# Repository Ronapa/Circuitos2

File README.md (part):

# Trabajo Práctico de Diseño
## Diseño de Circuitos Electronicos (86.10) - Primer cuatrimestre 2019
## Diseño de un Circuito amplificador clase G paralelo.
#### Integrantes: 
#####  Rodrigo Nahuel Parra - Padrón: 98785 - email: [ro.nahuel95@gmail.com](mailto:ro.nahuel95@gmail.com)
#####  Gonzalo Gilces Duran - Padrón: 99074 - email: [gonzalo.gilces@hotmail.com](mailto:gonzalo.gilces@hotmail.com)
#####  Segundo Molina Abeniacar - Padrón: 99306 - email: [segun_m@hotmail.com](mailto:segun_m@hotmail.com)
#### Tutor:
##### Edgardo Marchi - email: [edgardo.marchi@gmail.com](mailto:edgardo.marchi@gmail.com)

#### Índice
* [Resumen](https://github.com/Ronapa/Circuitos2/#resumen)  
* [Diseño](https://github.com/Ronapa/Circuitos2/#diseño)  
  * [Polarización y funcionamiento del circuito](https://github.com/Ronapa/Circuitos2/#polarización-y-funcionamiento-del-circuito)  
    * [Etapa de entrada](https://github.com/Ronapa/Circuitos2/#etapa-de-entrada)  
    * [Etapa VAS y multiplicador de Vbe](https://github.com/Ronapa/Circuitos2/#etapa-vas-y-multiplicador-de-vbe)
    * [Etapa de salida](https://github.com/Ronapa/Circuitos2/#etapa-de-salida)
    * [Switches y conmutación](https://github.com/Ronapa/Circuitos2/#switches-y-conmutación)
    * [Fuentes switching](https://github.com/Ronapa/Circuitos2/#fuentes-switching)
    * [Análisis de la amplificación](https://github.com/Ronapa/Circuitos2/#análisis-de-la-amplificación)
  * [Elección de las tencologías utilizadas](https://github.com/Ronapa/Circuitos2/#elección-de-las-tecnologías-utilizadas)
  * [Compensación del circuito y respuesta en frecuencia](https://github.com/Ronapa/Circuitos2/#compensación-del-circuito-y-respuesta-en-frecuencia)
  * [Potencia y eficiencia](https://github.com/Ronapa/Circuitos2/#potencia-y-eficiencia)
    * [Potencia en la carga](https://github.com/Ronapa/Circuitos2/#potencia-en-la-carga)
    * [Eficiencia del circuito](https://github.com/Ronapa/Circuitos2/#eficiencia-del-circuito)
    * [Potencia disipada en los transistores](https://github.com/Ronapa/Circuitos2/#potencia-disipada-en-los-transistores)
  * [Ensayos variando la carga](https://github.com/Ronapa/Circuitos2/#ensayos-variando-la-carga)
  * [Simulaciones sobre el amplificador](https://github.com/Ronapa/Circuitos2/#simulaciones-sobre-el-amplificador)
    * [Impedancia de entrada y salida](https://github.com/Ronapa/Circuitos2/#impedancia-de-entrada-y-salida)
    * [Limitación de corriente y protecciones](https://github.com/Ronapa/Circuitos2/#limitación-de-corriente-y-protecciones)
    * [Rechazo de ruido de la fuente](https://github.com/Ronapa/Circuitos2/#rechazo-de-ruido-de-la-fuente)
    * [Limitaciones sobre los valores de alimentación](https://github.com/Ronapa/Circuitos2/#limitaciones-sobre-los-valores-de-alimentación)
  * [Diseño del PCB](https://github.com/Ronapa/Circuitos2/#diseño-del-pcb)
* [Especificaciones](https://github.com/Ronapa/Circuitos2/#especificaciones)
* [Construcción](https://github.com/Ronapa/Circuitos2/#construcción)
  * [Implementación de la etapa de entrada](https://github.com/Ronapa/Circuitos2/#implementación-de-la-etapa-de-entrada)
* [Problemas y plan](https://github.com/Ronapa/Circuitos2/#problemas-y-plan)  
### Resumen
El objetivo de este trabajo fue diseñar un amplificador de audio clase G con la etapa de salida conmutada en paralelo. La principal motivación fué la de mejorar la excursión del amplificador ya que el amplificador clase G clásico, posee los dos transistores de salida en serie, lo que provoca que cuando está activada la etapa del riel de mayor tensión, la señal también debe circular a través del otro transistor, generando disipaciones de potencia innecesaria y pérdida de excursión al tener la caída de colector-emisor de dos transistores. Se puso como objetivo diseñar un circuito que amplifica una señal de audio estándar 1VRMS a la máxima tensión posible para cargas de 4 y 8 Ohms. Otra especificación fue la de la potencia, la cual se estimó alrededor de los 45-50W para una carga de 8Ohms. El amplificador es alimentado con una fuente de ±30V y una de ±15V. Estos valores de tensión se logran con una fuente de laboratorio de ±30V y una fuente switching que otorga los valores de ±15 necesarios. El circuito cuenta con un LED de encendido, y una protección por sobrecorriente. 

## Diseño
El circuito fue diseñado en base al amplificador [Kenwood KA-7X](http://materias.fi.uba.ar/6610/Manuales%20de%20servicio%20tecnico/Clase%20G%20y%20H/Kenwood/KA-7X/hfe_kenwood_ka_7x_service.pdf). Este es un amplificador _stereo_ clase G con etapa de salida en paralelo. Nuestro amplificador, en cambio, es de tipo _mono_. El circuito diseñado está basado en etapas definidas por el circuito en bloques de la siguiente figura.

![Circuito en bloques][Circuito en bloques]

Nuestro circuito simulado se encuentra a continuación:

![Circuito LTSpice][Nuestro Circuito]

Se optó hacer un circuito clase G porque con este logra una elevada eficiencia en amplificación de audio. Esto se debe a que, en audio, los transistores de mayor tensión funcionan en intervalos cortos de tiempo, siendo los de menor señal los que conducen la mayor parte. Esto se debe a que las señales de audio que se reproducen generalmente tienen un alto cociente de valor pico a valor medio, esto es, los momentos de señales altas son breves y pocos. Además, al plantear la etapa de salida con los transistores en paralelo, se logró aumentar aún más la eficiencia, ya que en cualquier momento solo está conduciendo un transistor. En cambio, si la salida estuviera en serie, en los momentos de alta señal conducirían los dos transistores de salida. 

### Polarización y funcionamiento del circuito
#### Etapa de entrada
La etapa de entrada del circuito es un amplificador diferencial con carga activa, estabilizado mediante realimentación por emisor para las diferencias entre los _betas_ de los transistores. Cada rama del par diferencial está polarizada con 500uA, y por Q5 circula una corriente de 1mA. El capacitor C1 se encuentra para filtrar la tensión de continua de la entrada, de este modo el circuito solo amplfica tensiones de señal.  

El rol de la etapa de entrada es obtener la diferencia entre la entrada y la realimentación y generar la señal error que se amplifica en el circuito hasta llegar a la salida. Esta es una etapa de amplificación de transconductancia, que según la entrada diferencial impone una corriente en la base de Q23, la etapa de VAS. Es primordial que en esta etapa no se distorsione la señal, y para esto tenemos poder linealizar respecto de nuestro punto de polarización. Con esto en mente justificamos la carga activa para asegurar corrientes iguales de polarización en el par. Si bien existen mejores modelos de fuentes espejo, el resultado obtenido con una fuente espejo simple hacía que no se justificara implementar modelos que dificultarían su implementación y aumentaría el costo del proyecto.  

En una base del diferencial se encuentra la señal de entrada mientras que en la otra se encuentra R39 que se conecta a la salida. Esta resistencia cumple dos funciones, por un lado polariza al circuito de entrada y por otro junto con R9 tiene realimentación para señal. El análisis de realimentación se encuentra en la sección [Análisis de la amplificación](https://github.com/Ronapa/Circuitos2/#análisis-de-la-amplificación). 

La etapa de entrada esta cargada con la etapa del VAS, conectado mediante la base de Q23. Este transistor está polarizado con 721uA, lo del cual obtenemos 

 , 

la cual está en serie con el paralelo de R42 y r_{pi} de Q6 multiplicado por beta, aproximadamente 4kOhms. Finalmente, la etapa de entrada está cargada con 7.6kOhms. 

![Etapa de entrada][Etapa Entrada]

#### Etapa VAS y multiplicador de Vbe
Una vez definida preliminarmente la etapa de salida se prosiguió con el VAS, o Voltage Amplifier Stage. Uno de los primeros inconvenientes encontrados fue que la etapa de salida consumía una corriente excesiva de la etapa de entrada, lo que causaba que los transistores de la segunda etapa entraran en corte y distorsionaran la señal. La solución planteada fue agregar un Darlinton a la salida del par diferencial, de este modo consumía menos corriente de la etapa de entrada. Por la malla del multiplicador de Vbe y por Q8 circula una corriente de 4.4mA de polarización. En señal, esta corriente varía en menos de 20uA, ya que la corriente que entrega la señal a la  etapa de salida está dada por los dos seguidores formados por Q25-Q26 y Q24-Q27. 

![Etapa de VAS][Etapa VAS]

La tensión a la salida de esta etapa, tiene un desnivel de 2Vbe por la caida en los transistores de los seguidores, sin embargo, ajustando el valor de la resistencia R12 logramos que el multiplicador de Vbe equipare este desnivel. Esto se ve en la siguiente imagen, donde se aprecia que esta etapa amplifica tensión y copia la señal a las dos ramas de la salida, con la diferencia de los Vbe necesarios para obtener una señal sin distorsión. 

![Diferencia_VAS][Diferencia_VAS]

#### Etapa de salida
La etapa de salida, como se ve en la imagen, es simétrica para el camino de señal del semicilco positivo y del negativo. A continuación se hará un analisis del camino de señal positiva de esta etapa siendo los resultados análogos para el camino de señal negativa.  
Primero, Q11 y Q12 funcionan como llaves, controladas por los circuitos de conmutación. Q11 permanece sin conducir hasta que se lo indica la señal _S\_HIGH_. Una vez que Q11 conduce la tensión en su colector es mayor a la del emisor de Q12, por lo que Q12 entra en corto. De este modo solo conduce una rama a la vez. Esta topología de tener los transistores en paralelo mejora la efciencia, ya que no se tiene conduciendo constantemente al transistor de baja tensión como en un amplificador clase G serie.   
Para la salida de tensión alta se planteó un Darlington, de manera de reducir la corriente consumida por la etapa de salida, lo que producía que los transistores de etapas anteriores distorsionaran la señal. Esto se debe a que la corriente de colector de estos transistores es grande y su _beta_ es chico, del orden de 50, ya que se trata de transistores de potencia. Planteando el darlington se resuelve esta problemática.   
Para la entrada sin señal se obtuvo un valor de -1.6mV a la salida, lo cual es más que aceptable.

Una vez determinada la etapa de salida y con un resultado dentro de los márgenes esperados se agregó una protección de sobrecorriente para proteger a los transistores de corrientes elevadas. Esta protección sensa la tensión sobre el resistor R15 y al superar el valor de aproximadamente 0.7V se enciende el transistor Q29, tomande corriente de la base de la etapa de salida, disminuyendo la corriente de base y por lo tanto la que se dirige a la carga. Como el amplificador esta diseñado para cargas de 4 y 8 Omhs se buscó limitar la corriente a alrededor de 8A. Además el transistor se encuentra polarizado con un LED lo que permite tener un indicador visual de si la protección esta siendo activada. Como se mencionó anteriormente, la etapa del semiciclo negativo fuinciona de manera análoga.

Si bien esta protección resulta útil para proteger los transistores frente a una carga de bajo valor, como por ejemplo 2 Omhs, no resulta del todo eficiente para un corto a la salida. El objetivo es que si se coloca un amplificador de una impedancia incorrecta, o en su defecto 2 amplificadores de 4 Omhs en paralelo, el amplificador no trate de entregar toda la potencia a la carga quemando la etapa de salida. Por como se diseño la protección, frente a un corto en la salida se produce una limitación a una corriente de 16A, lo cual es destructivo para el transistor. Sin embargo, según la hoja de datos el transistor puede tolerar picos de hasta 30A por menos de 1ms. Es por esto que además se colocará en la alimentación un fusible de manera de que llegado el caso de que se produzca un corto a la salida el amplificador no se destruya. Una mejora posible sería plantear un circuito con un rele que abra el circuito de manera de no tener que cambiar un fusible.

![Etapa de Salida][Etapa salida]

#### Switches y conmutación
A continuación se encuentra el circuito que controla la conmutación entre el camino de señal alta y el de baja. La salida de este circuito se conecta a la base de Q11 como se planteó en la sección anterior. 

![Etapa conmutacion][Etapa Switches]

Primero se plantea un divisor resistivo con R17 y R18, de donde se obtiene una tensión de referencia. La tensión de referencia simulada es de 11.95V. Se eligió este valor para que la señal no se acerque demasiado a 15V antes de conmutar, dado que esto podía producir que algún transistor sature deformando la señal. Cuando la salida supera este valor, Q13 entra en conducción. Cuando esto ocurre, empieza a circular una corriente sobre  R19 y R20, que a su vez polariza a Q14. Este último es el que toma corriente de la base del switch y así cambiando el circuito de señal.  
La resistencia R26 es un realimentador que muestrea la tensión de la referencia y entrega corriente al transistor Q14 para estabilizar la señal. Finalmente, la rama de C3 filtra componentes de alta frecuencia dadas por la conmutación rápida. 

![Conmutacion][Conmutación circuitos]

#### Fuentes switching

Las fuentes switching están planteadas para entregar potencia a los transistores de menor potencia. Se eligió esta tecnología por la eficicencia que tiene para bajar la tensión de 30V de la fuente de laboratorio a los 15V que necesitamos en el circuito. En la siguiente imagen se muestra el circuito que compone a la fuente switching, el cual fue simulado en el entorno [Webench Power Designer de Texas Instruments.](https://webench.ti.com/power-designer/switching-regulator)

![Fuente switching][fuente switching]

En las siguientes imagenes se puede ver como al conmutar se tiene un transitorio que se extingue dejando finalmente una señal triangular, al rededor del valor que queremos obtener. 

![switching load transient][switching load transient]

![switching input transient][switching input transient]

La siguiente imagen muestra el estado estacionario de la fuente conmutada, donde se ve una señal triangular de 60mVpico. 

![switching steady][switching steady]

Este ruido en la fuente podría ser reflejado en la señal de salida, sin embargo las entradas de las fuentes switching al circuito tienen un capacitor que filtra las componentes de alta frecuencia. Finalmente, para la señal restante que entra al circuito, si bien no es perfectamente plana, mediante simulaciones se comprobó que variaciones menores a 1V en las fuentes no se reflejan en la salida. 

A estas especificaciones, además, se le agregó la consideración del costo. Armar una fuente switching es más barato y eficiente que circuitos más complejos que modulen la señal de modo de no tener nada de variaciones en la salida. 

#### Análisis de la amplificación

Para hacer un análisis de la amplificación, primero separamos por etapas, según el diagrama en bloques de la [figura](https://github.com/Ronapa/Circuitos2#dise%C3%B1o). De acuerdo a esto obtuvimos la amplificación de las distintas etapas. Para empezar, la etapa de salida como gana corriente la amplificación en tensión es aproximadamente 1. La amplificación de la etapa de entrada se calcula como 

donde Rca es la resistencia que carga a la etapa de entrada. De acuerdo a esto la amplificación de la etapa de entrada es |a1|=230.

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
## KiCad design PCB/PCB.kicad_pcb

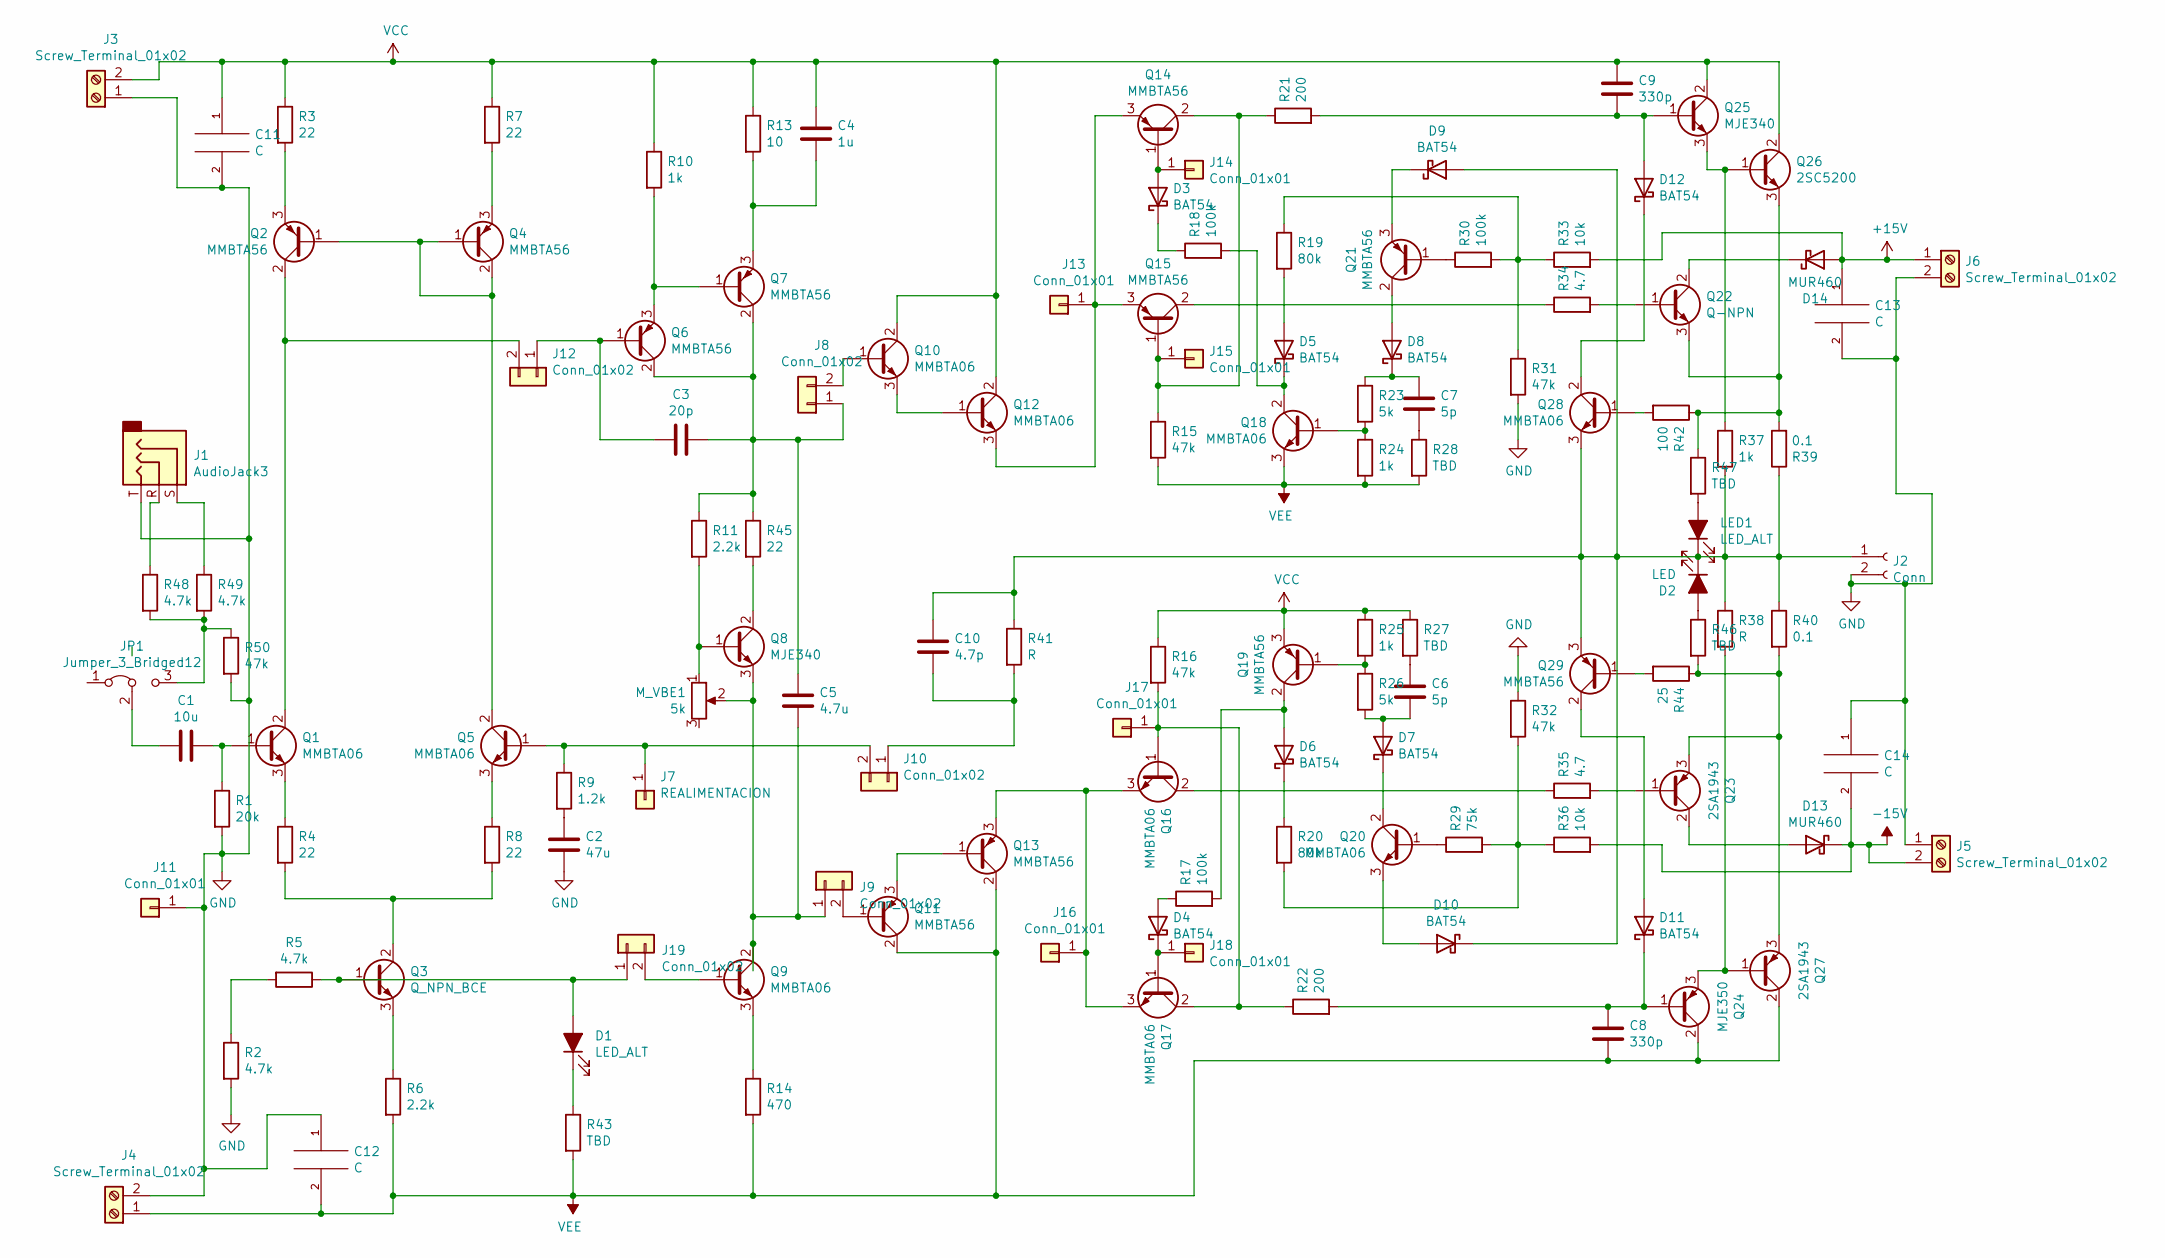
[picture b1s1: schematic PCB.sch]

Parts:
C1: 10u; CP_Radial_D5.0mm_P2.50mm
C2: 47u; CP_Radial_D5.0mm_P2.00mm
C3: 20p; C_1206_3216Metric_Pad1.33x1.80mm_HandSolder
C4: 1u; C_1206_3216Metric_Pad1.33x1.80mm_HandSolder
C5: 4.7u; CP_Radial_D5.0mm_P2.00mm
C6, C7: 5p; C_1206_3216Metric_Pad1.42x1.75mm_HandSolder
C8, C9: 330p; C_1206_3216Metric_Pad1.42x1.75mm_HandSolder
C10: 4.7p; C_1206_3216Metric_Pad1.33x1.80mm_HandSolder
C11, C12, C13, C14: C; C_Radial_D18.0mm_H35.5mm_P7.50mm
D1: LED_ALT; LED_D5.0mm
D2: LED; LED_D5.0mm
D3, D4, D5, D6, D7, D8, D9, D10, D11, D12: BAT54; D_SOT-23_ANK
D13, D14: MUR460; D_DO-41_SOD81_P10.16mm_Horizontal
J1: AudioJack3; Jack_3.5mm_CUI_SJ-3523-SMT_Horizontal
J2: Conn; GTK2400-V2
J3, J4, J5, J6: Screw_Terminal_01x02; JWT_A3963_1x02_P3.96mm_Vertical
J7: REALIMENTACION; PinHeader_1x01_P2.54mm_Vertical
J8, J9, J10, J12, J19: Conn_01x02; PinHeader_1x02_P2.54mm_Vertical
J11, J13, J14, J15, J16, J17, J18: Conn_01x01; PinHeader_1x01_P2.54mm_Vertical
JP1: Jumper_3_Bridged12; PinHeader_1x03_P2.54mm_Vertical
LED1: LED_ALT; LED_D5.0mm
M_VBE1: 5k; Potentiometer_Bourns_3266Y_Vertical
Q1, Q5, Q9, Q10, Q12, Q16, Q17, Q18, Q20, Q28: MMBTA06; SOT-23_Handsoldering
Q2, Q4, Q6, Q7, Q11, Q13, Q14, Q15, Q19, Q21, Q29: MMBTA56; SOT-23_Handsoldering
Q3: Q_NPN_BCE; SOT-23_Handsoldering
Q8: MJE340; TO-126-3_Vertical
Q22: Q-NPN; TO-3P-3_Vertical
Q23, Q27: 2SA1943; TO-3P-3_Vertical
Q24: MJE350; SOT-23_Handsoldering
Q25: MJE340; SOT-23_Handsoldering
Q26: 2SC5200; TO-3P-3_Vertical
R1: 20k; R_0805_2012Metric_Pad1.15x1.40mm_HandSolder
R2, R5, R48, R49: 4.7k; R_1206_3216Metric_Pad1.30x1.75mm_HandSolder
R3, R4, R7, R8, R45: 22; R_1206_3216Metric_Pad1.30x1.75mm_HandSolder
R6, R11: 2.2k; R_1206_3216Metric_Pad1.30x1.75mm_HandSolder
R9: 1.2k; R_1206_3216Metric_Pad1.30x1.75mm_HandSolder
R10, R24, R25, R37: 1k; R_1206_3216Metric_Pad1.30x1.75mm_HandSolder
R13: 10; R_1206_3216Metric_Pad1.30x1.75mm_HandSolder
R14: 470; R_1206_3216Metric_Pad1.30x1.75mm_HandSolder
R15, R16, R31, R32, R50: 47k; R_1206_3216Metric_Pad1.30x1.75mm_HandSolder
R17, R18, R30: 100k; R_1206_3216Metric_Pad1.30x1.75mm_HandSolder
R19: 80k; R_0805_2012Metric_Pad1.15x1.40mm_HandSolder
R20: 80k; R_1206_3216Metric_Pad1.30x1.75mm_HandSolder
R21, R22: 200; R_1206_3216Metric_Pad1.30x1.75mm_HandSolder
R23, R26: 5k; R_1206_3216Metric_Pad1.30x1.75mm_HandSolder
R27, R28, R43, R46, R47: TBD; R_1206_3216Metric_Pad1.30x1.75mm_HandSolder
R29: 75k; R_1206_3216Metric_Pad1.30x1.75mm_HandSolder
R33, R36: 10k; R_1206_3216Metric_Pad1.30x1.75mm_HandSolder
R34, R35: 4.7; R_1206_3216Metric_Pad1.30x1.75mm_HandSolder
R38, R41: R; R_1206_3216Metric_Pad1.30x1.75mm_HandSolder
R39, R40: 0.1; R_Axial_Power_L25.0mm_W9.0mm_P7.62mm_Vertical
R42: 100; R_1206_3216Metric_Pad1.30x1.75mm_HandSolder
R44: 25; R_1206_3216Metric_Pad1.30x1.75mm_HandSolder

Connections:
+15V: C13.1, D14.2 (A), J6.1, R33.2
-15V: C14.2, D13.1 (K), J5.2, R36.2
GND: C2.1, C11.2, C12.1, C13.2, C14.1, J1.T, J2.2, J3.1, J4.2, J5.1, J6.2, J11.1, R1.2, R2.2, R31.2, R32.1, R50.2
unnamed: C1.1, JP1.2 (C)
unnamed: C1.2, Q1.1 (B), R1.1
unnamed: C2.2, R9.2
unnamed: C3.1, J12.1, Q6.1 (B)
unnamed: C3.2, C5.2, J8.1, Q6.2 (C), Q7.2 (C), R11.1, R45.1
unnamed: C4.1, Q7.3 (E), R13.2
unnamed: C5.1, J9.1, M_VBE1.2, Q8.3 (E), Q9.2 (C)
unnamed: C6.1, D7.2 (A), R26.2
unnamed: C6.2, R27.2
unnamed: C7.1, R28.1
unnamed: C7.2, D8.1 (K), R23.1
unnamed: C8.2, D11.1 (K), Q24.1 (B), R22.2
unnamed: C9.1, D12.2 (A), Q25.1 (B), R21.2
unnamed: C10.1, J10.1, R41.2
unnamed: C10.2, D2.1 (K), D9.2 (A), D10.1 (K), J2.1, LED1.1 (K), Q28.3 (E), Q29.3 (E), R37.2, R38.1, R39.1, R40.1, R41.1
unnamed: D1.1 (K), R43.1
unnamed: D1.2 (A), J19.1, Q3.1 (B), R5.1
unnamed: D2.2 (A), R46.1
unnamed: D3.1 (K), R18.1
unnamed: D3.2 (A), J14.1, Q14.1 (B)
unnamed: D4.1 (K), J18.1, Q17.1 (B)
unnamed: D4.2 (A), R17.1
unnamed: D5.1 (K), Q18.2 (C), R18.2
unnamed: D5.2 (A), R19.2
unnamed: D6.1 (K), R20.1
unnamed: D6.2 (A), Q19.2 (C), R17.2
unnamed: D7.1 (K), Q20.2 (C)
unnamed: D8.2 (A), Q21.2 (C)
unnamed: D9.1 (K), Q21.3 (E)
unnamed: D10.2 (A), Q20.3 (E)
unnamed: D11.2 (A), Q29.2 (C)
unnamed: D12.1 (K), Q28.2 (C)
unnamed: D13.2 (A), Q23.2 (C)
unnamed: D14.1 (K), Q22.2 (C)
unnamed: J1.R, R48.1
unnamed: J1.S, R49.1
unnamed: J8.2, Q10.1 (B)
unnamed: J9.2, Q11.1 (B)
unnamed: J7.1, J10.2, Q5.1 (B), R9.1
unnamed: J12.2, Q1.2 (C), Q2.2 (C)
unnamed: J13.1, Q12.3 (E), Q14.3 (E), Q15.3 (E)
unnamed: J15.1, Q14.2 (C), Q15.1 (B), R15.1, R21.1
unnamed: J16.1, Q13.3 (E), Q16.3 (E), Q17.3 (E)
unnamed: J17.1, Q16.1 (B), Q17.2 (C), R16.2, R22.1
unnamed: J19.2, Q9.1 (B)
unnamed: JP1.3 (B), R48.2, R49.2, R50.1
unnamed: LED1.2 (A), R47.2
unnamed: M_VBE1.1, Q8.1 (B), R11.2
unnamed: Q1.3 (E), R4.1
unnamed: Q2.1 (B), Q4.1 (B), Q4.2 (C), Q5.2 (C)
unnamed: Q2.3 (E), R3.2
unnamed: Q3.2 (C), R4.2, R8.2
unnamed: Q3.3 (E), R6.1
unnamed: Q4.3 (E), R7.2
unnamed: Q5.3 (E), R8.1
unnamed: Q6.3 (E), Q7.1 (B), R10.2
unnamed: Q8.2 (C), R45.2
unnamed: Q9.3 (E), R14.1
unnamed: Q10.3 (E), Q12.1 (B)
unnamed: Q11.3 (E), Q13.1 (B)
unnamed: Q15.2 (C), R34.1
unnamed: Q16.2 (C), R35.1
unnamed: Q18.1 (B), R23.2, R24.1
unnamed: Q19.1 (B), R25.2, R26.1
unnamed: Q20.1 (B), R29.1
unnamed: Q21.1 (B), R30.1
unnamed: Q22.1 (B), R34.2
unnamed: Q22.3 (E), Q26.3 (E), R39.2, R42.1, R47.1
unnamed: Q23.1 (B), R35.2
unnamed: Q23.3 (E), Q27.3 (E), R40.2, R44.1, R46.2
unnamed: Q24.3 (E), Q27.1 (B), R38.2
unnamed: Q25.3 (E), Q26.1 (B), R37.1
unnamed: Q28.1 (B), R42.2
unnamed: Q29.1 (B), R44.2
unnamed: R2.1, R5.2
unnamed: R19.1, R30.2, R31.1, R33.1
unnamed: R20.2, R29.2, R32.2, R36.1
VCC: C4.2, C9.2, C11.1, J3.2, Q10.2 (C), Q12.2 (C), Q19.3 (E), Q25.2 (C), Q26.2 (C), R3.1, R7.1, R10.1, R13.1, R16.1, R25.1, R27.1
VEE: C8.1, C12.2, J4.1, Q11.2 (C), Q13.2 (C), Q18.3 (E), Q24.2 (C), Q27.2 (C), R6.2, R14.2, R15.2, R24.2, R28.2, R43.2

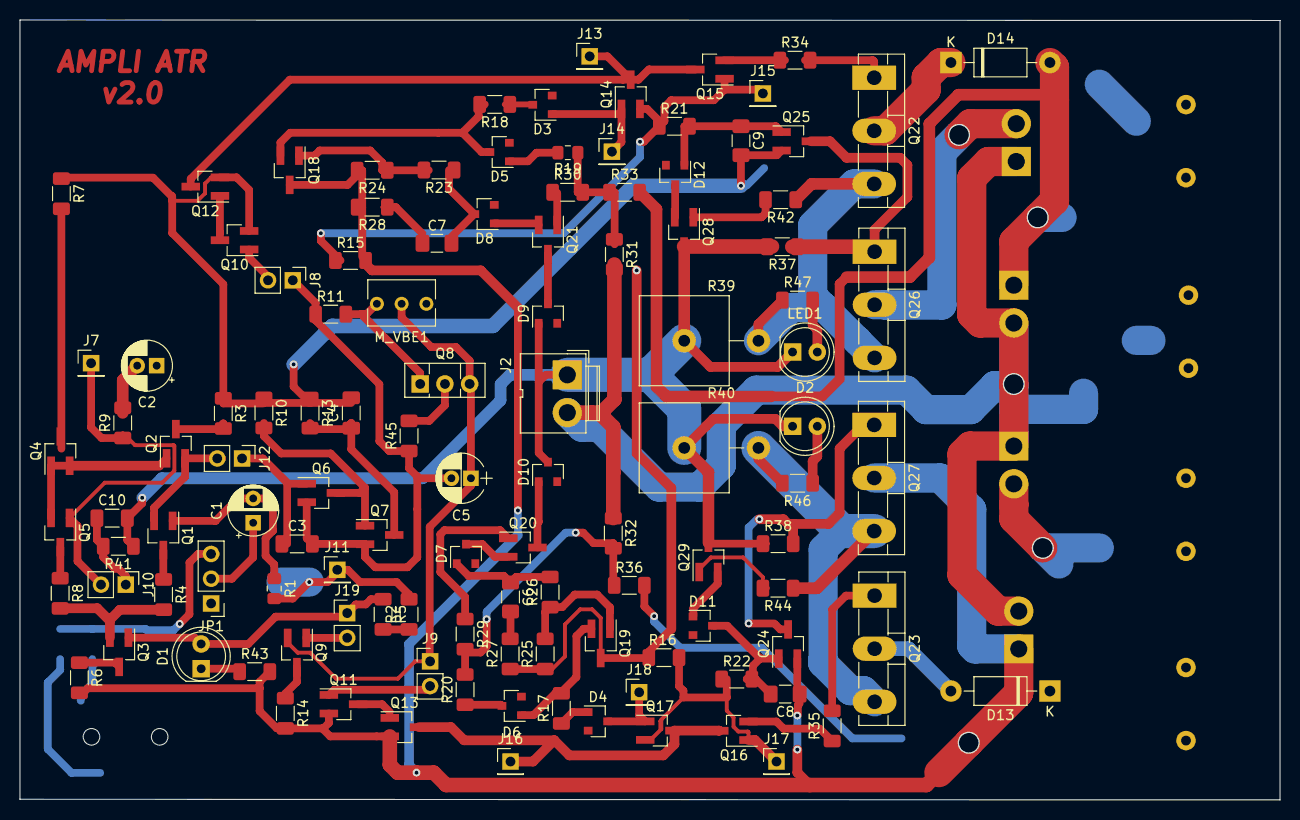
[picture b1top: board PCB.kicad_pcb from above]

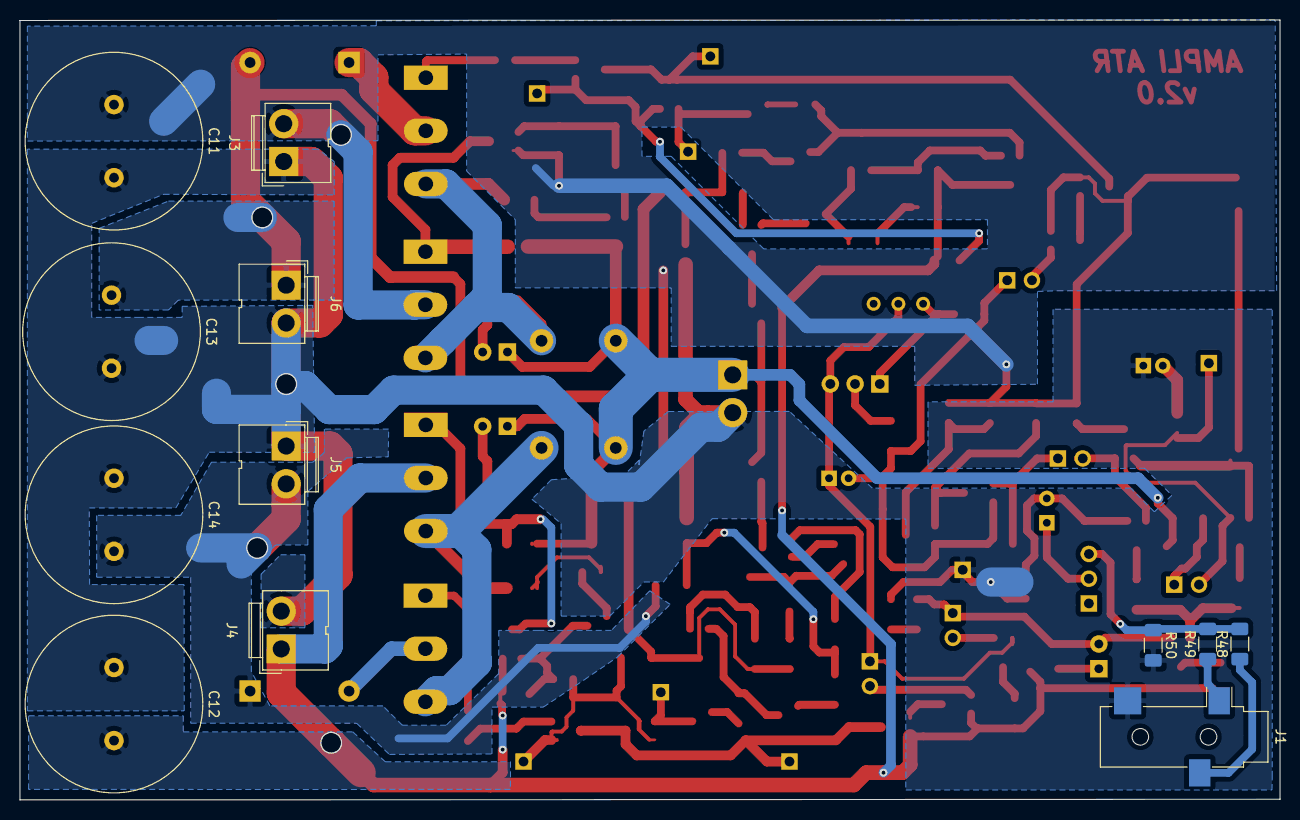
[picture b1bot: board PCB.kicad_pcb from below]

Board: 2 copper layers, 129.3 x 80.1 mm, 128 parts (12 on the bottom side), 82 nets.

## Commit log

2019-05-18 Create TP_FINAL
2019-05-26 Diseño serie
2019-05-26 Organizo
2019-05-26 Agrego bibliografia
2019-05-26 Primer intento de diseño del amplificador en modo paralelo. No me sale hacer el switch de 20 a 40
2019-05-27 Avanzo con el diseño del conmutador (copiado de la referencia)
2019-06-01 Circuito generico andando
2019-06-05 Etapa de entrada agregada
2019-06-07 Falta poner modelos etapa de entrada
2019-06-14 transistores BC850 y BC860 en etapa de entrada
2019-06-14 Saqué el capacitor que bajaba la impedancia en alterna
2019-06-16 Darlington a la salida y caps para sacar alta frec
2019-06-16 Saqué el cap a la salida que me metia error en frec
2019-06-16 Revert "Update TPdisenio.asc"
    This reverts commit 83d8e3645f74142528650de193df0f94e8c26536.
2019-06-16 Revert "Saqué el cap a la salida que me metia error en frec"
    This reverts commit 461378c1494e3d230b2a1ca4f1534f82aeaf58cf.
2019-06-16 Revert "Revert "Update TPdisenio.asc""
    This reverts commit 1e941105a8bf221419f007b5ee4837c5abc4cf99.
2019-06-17 Cambie un par de valores y baje la distorsion a 0.5%
2019-06-28 update analisis
2019-06-28 subo imagenes y reacomode el circuito
2019-06-28 agrego imagenes
2019-06-28 mas imagenes
2019-06-28 agrego diodos
2019-06-28 0.005% THD 8Omhs - 0.008% THD 4Ohms
2019-06-28 Arregle lo del switch
2019-06-28 Update imágenes
2019-06-28 update der no se q
2019-06-29 no se
2019-06-29 cree carpeta para ordenar un poco
2019-06-29 Agrego imagen circuito e bloques
2019-06-29 Cambie para que el circuito apunte a las librerias
2019-07-02 Cambio de resistencia de emisor y los 2 diodos
2019-07-03 Mejora distorsion
2019-07-03 Revert "Mejora distorsion"
    This reverts commit 17f80820dcecb12f95c796370ffeefb619a687be.
2019-07-04 Cambios de valores
2019-07-04 Cambie valores
2019-07-04 Diodos baje picos de corriente pero baja amp salida
2019-07-04 Update TPdiseno
2019-07-04 Revert "Revert "Mejora distorsion""
    This reverts commit 9add405717f3a4383635c6223eb876d9e912b0ec.
2019-07-04 Revert "Merge branch 'master' of https://github.com/Ronapa/Circuitos2"
    This reverts commit 1237e11fa7bcfd5d8bb9da1045e174d638bc404e, reversing
    changes made to fc237089ef3b3c19cfe880d44f1780a468d29e51.
2019-07-04 Revert "Revert "Revert "Mejora distorsion"""
    This reverts commit fc237089ef3b3c19cfe880d44f1780a468d29e51.
2019-07-04 Revert "Revert "Revert "Revert "Mejora distorsion""""
    This reverts commit f20339544ab76ca368cfaed3decdf621eede3481.
2019-07-04 Revert "Revert "Revert "Revert "Revert "Mejora distorsion"""""
    This reverts commit 6cb80f54d3c83c08c66f6e67b0f9ac97b4dc8910.
2019-07-04 Restauro a donde lo dejo second
2019-07-04 Cambie valores y anda mejor
    Cambie valores
2019-07-04 nueva imagen
2019-07-04 gato
2019-07-04 Alternativa al switch
2019-07-05 Limitador de corriente andanding
2019-07-05 Imagenes y compensacion
2019-07-05 Circuito andando y flama para sacar screens
2019-07-05 readme
2019-07-18 update pcb
2019-07-20 Etapa salida PCB cheta
2019-07-21 pcb update
2019-07-21 pcb v1.0
2019-07-21 potenciometro xVbe
2019-07-21 update imagenes
2019-07-21 update readme e imagenes
2019-07-24 update fotos, readme y rout
2019-07-26 disipadores
2019-07-26 update imagens
2019-07-27 update switching
2019-07-27 fuente sw
2019-07-31 curvas de eficiencia
2019-07-31 Para graficar en funcion de algo
2019-07-31 imagenes compensacion
2019-07-31 update algunas imagenes
2019-07-31 respuesta pulsos
2019-10-09 Agregados los capacitores de alimentacion, pistas a las borneras sobre cara superior y a capacitores por cara inferior. Faltaría acomodar los FILL
2019-10-11 rellené capas de abajo
2019-10-12 Rellenos PROLIJOS, Jack 3.5mm
2019-10-12 update de lo charlado con edgar
2019-10-14 Jack 3.5mm girado
2019-10-15 Pistas emprolijadas
2019-10-16 Grosor de pistas verificadas, incorporacion via para capacitor realimentacion
2019-10-25 Se saco la conexion a GND de la entrada y se agregaron unas vias
2019-10-25 final final
2019-11-04 cosas para mandar a imprimir
2020-01-21 chequeate esta rodre
2020-01-21 ahi va
2020-01-21 ahora sí
2021-02-27 Footprint actualizados. se agrando el pcb para los capacitores. Se agregaron algunos valores de componentes en el esquematico
2021-03-01 Completed all values of components. Added VCC & VDD in switches. Added missing diodes. Added LEDs to current limiter
2021-03-01 Modified names to be the same as the PCB
2021-03-01 More footprint changes. Added some modifications to the pcb
2021-03-02 Updated D13 & D14 diode for MUR460. Updated he PCB and verified conections
2021-03-04 Added pins to make measurements. Added jumpers to devide circuits
2021-03-05 Added resistors for miniplugs. Added name to pcb. Small modifications
2021-05-26 Agrego carpeta de Simulaciones. Simulación de eficiencia andando
2021-05-26 Simulacion de Zin y Zout
2021-05-29 cambie la R de realimetnacion por 18k
2021-05-29 gregue compensacion
2021-06-07 Simulacion de distorsion y eficiencia
2021-06-12 cambie caps de compensaciÃn
2021-06-12 Subo un par de simulaciones y cambio un par de cosas en Zin y Zout
2021-06-13 AgreguÃ slew rate
2021-06-13 Distorsion simulada de nuevo. Agrego distorsion por intermodulasion
2021-06-16 Actualizacion de intermodulacion
2021-06-21 grego limitacion corriente
2021-06-21 mediciones laboratorio
